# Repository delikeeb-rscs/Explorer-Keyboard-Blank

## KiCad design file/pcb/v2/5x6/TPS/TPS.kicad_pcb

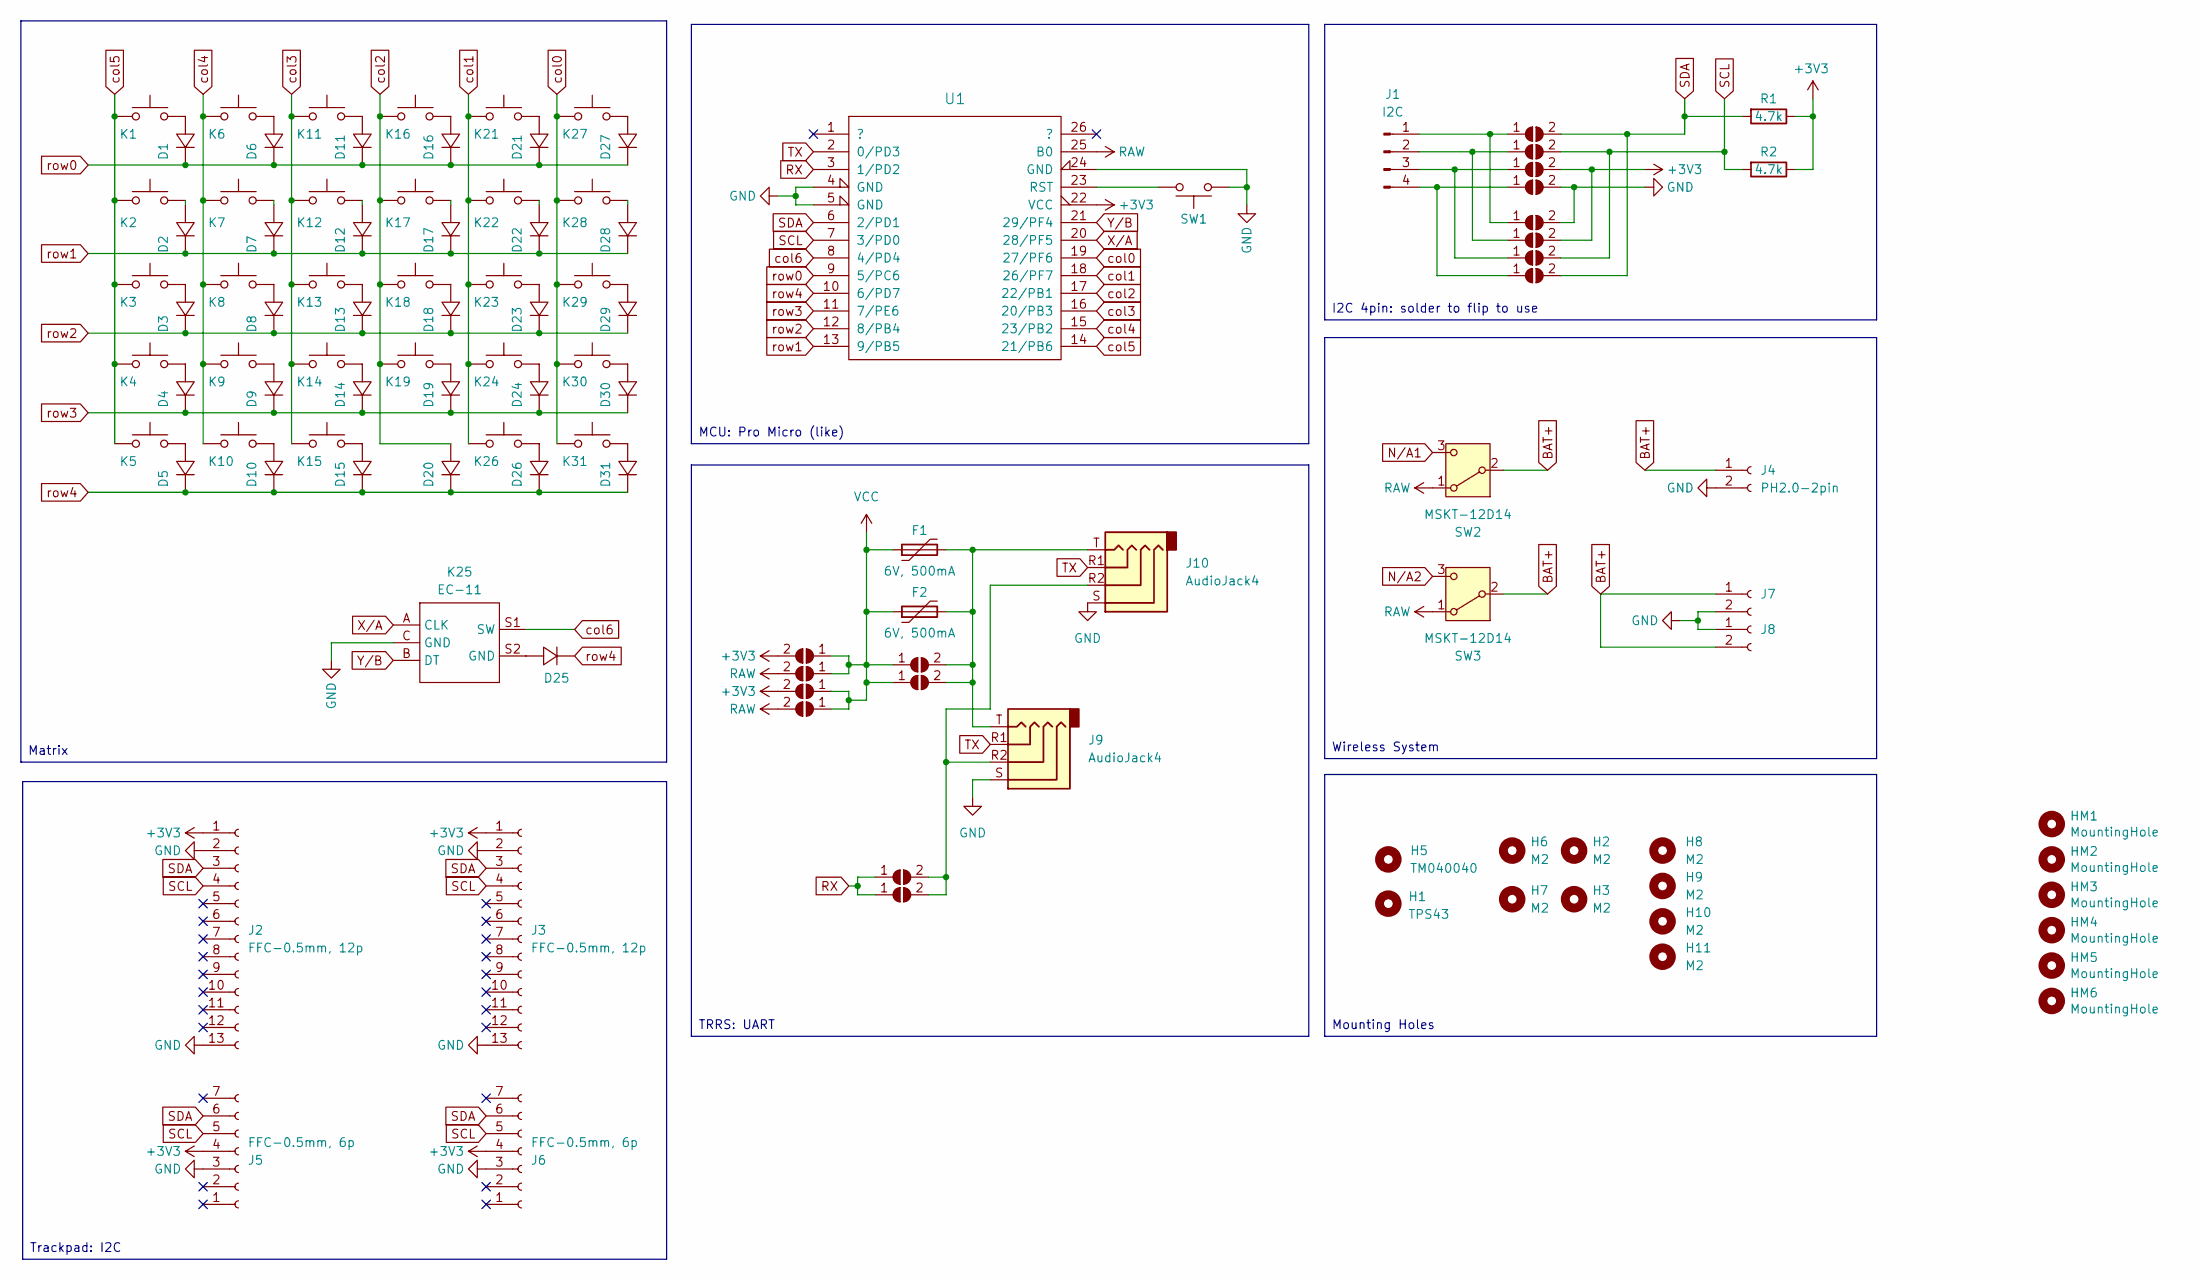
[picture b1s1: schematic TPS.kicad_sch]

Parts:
D1, D2, D3, D4, D5, D6, D7, D8, D9, D10, D11, D12, D13, D14, D15, D16, D17, D18, D19, D20, D21, D22, D23, D24, D25, D26, D27, D28, D29, D30, D31: 1N4148_SMD; D_SOD-123_handsolder_dual
F1, F2: 6V, 500mA; Fuse_0805_2012Metric
H1: TPS43; Azoteq_TPS43_201A_S
H2, H3, H6, H7, H8, H9, H10, H11: M2; MountingHole_2.2mm_M2
H5: TM040040; Trackpad_Cirque_TM040040
HM1, HM2, HM3, HM4, HM5, HM6: MountingHole; MountingHole_2.2mm_M2_ISO7380_Pad_noSilk
J1: I2C; PinHeader_1x04_P2.54mm_Vertical
J2, J3: FFC-0.5mm, 12p; Hirose_FH12-12S-0.5SH_1x12-1MP_P0.50mm_Horizontal
J4: PH2.0-2pin; JST_PH_S2B-PH-K_1x02_P2.00mm_Horizontal_dual
J5, J6: FFC-0.5mm, 6p; Hirose_FH12-6S-0.5SH_1x06-1MP_P0.50mm_Horizontal
J7, J8: PinHeader_1x02_P2.54mm_Vertical
J9: AudioJack4; TRRS-PJ-320A, dual side x2
J10: AudioJack4; TRRS-PJ-320A, dual side x2_3rd
JP1, JP2, JP3, JP4: PWR1; SolderJumper-2_P1.3mm_Open_Pad1.0x1.5mm
JP5, JP6, JP7, JP8, JP9, JP10, JP11, JP12: PWR1; SolderJumper-2_P1.3mm_Open_RoundedPad1.0x1.5mm
JP13, JP14: RX; SolderJumper-2_P1.3mm_Open_RoundedPad1.0x1.5mm
JP15, JP16: VCC; SolderJumper-2_P1.3mm_Open_Pad1.0x1.5mm
K1, K2, K3, K4, K6, K7, K8, K9, K11, K12, K13, K14, K15, K16, K17, K18, K19, K21, K22, K23, K24, K27, K28, K29, K30: SW_Push; SW_hotswap_HLP_Plated_1u-reversible
K5, K10, K26, K31: SW_Push; SW_hotswap_HLP_Plated_1.25u-reversible
K25: EC-11; RotaryEncoder_EC11
R1, R2: 4.7k; R_Axial_DIN0204_L3.6mm_D1.6mm_P7.62mm_Horizontal
SW1: SW_Push; ResetSW_1side
SW2, SW3: MSKT-12D14; SW_SPDT_MSKT-12D14_SMD_dual
U1: MCU_ProMicro_13p; MCU_ProMicro_13p_dual

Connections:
+3V3: J2.1, J3.1, J5.4, J6.4, JP1.2 (B), JP3.2 (B), JP7.2 (B), JP10.2 (B), R1.1, R2.1, U1.22 (VCC)
BAT+: J4.1, J7.1, J8.2, SW2.2 (B), SW3.2 (B)
GND: J2.2, J2.13, J3.2, J3.13, J4.2, J5.3, J6.3, J7.2, J8.1, J9.S, J10.S, JP8.2 (B), JP9.2 (B), K25.C (GND), SW1.1, U1.4 (GND), U1.5 (GND), U1.24 (GND)
unnamed: D1.2, K1.2
unnamed: D2.2, K2.2
unnamed: D3.2, K3.2
unnamed: D4.2, K4.2
unnamed: D5.2, K5.2
unnamed: D6.2, K6.2
unnamed: D7.2, K7.2
unnamed: D8.2, K8.2
unnamed: D9.2, K9.2
unnamed: D10.2, K10.2
unnamed: D11.2, K11.2
unnamed: D12.2, K12.2
unnamed: D13.2, K13.2
unnamed: D14.2, K14.2
unnamed: D15.2, K15.2
unnamed: D16.2, K16.2
unnamed: D17.2, K17.2
unnamed: D18.2, K18.2
unnamed: D19.2, K19.2
unnamed: D21.2, K21.2
unnamed: D22.2, K22.2
unnamed: D23.2, K23.2
unnamed: D24.2, K24.2
unnamed: D25.2, K25.S2 (GND)
unnamed: D26.2, K26.2
unnamed: D27.2, K27.2
unnamed: D28.2, K28.2
unnamed: D29.2, K29.2
unnamed: D30.2, K30.2
unnamed: D31.2, K31.2
unnamed: J1.1, JP5.1 (A), JP9.1 (A)
unnamed: J1.2, JP6.1 (A), JP10.1 (A)
unnamed: J1.3, JP7.1 (A), JP11.1 (A)
unnamed: J1.4, JP8.1 (A), JP12.1 (A)
unnamed: J9.R2, J10.R2, JP13.2 (B), JP14.2 (B)
unnamed: F1.2, F2.2, J9.T, J10.T, JP15.2 (B), JP16.2 (B)
unnamed: SW1.2, U1.23 (RST)
N/A1: SW2.3 (C)
N/A2: SW3.3 (C)
RAW: JP2.2 (B), JP4.2 (B), SW2.1 (A), SW3.1 (A), U1.25 (B0)
RX: JP13.1 (A), JP14.1 (A), U1.3 (1/PD2)
SCL: J2.4, J3.4, J5.5, J6.5, JP6.2 (B), JP11.2 (B), R2.2, U1.7 (3/PD0)
SDA: J2.3, J3.3, J5.6, J6.6, JP5.2 (B), JP12.2 (B), R1.2, U1.6 (2/PD1)
TX: J9.R1, J10.R1, U1.2 (0/PD3)
VCC: F1.1, F2.1, JP1.1 (A), JP2.1 (A), JP3.1 (A), JP4.1 (A), JP15.1 (A), JP16.1 (A)
X/A: K25.A (CLK), U1.20 (28/PF5)
Y/B: K25.B (DT), U1.21 (29/PF4)
col0: K27.1, K28.1, K29.1, K30.1, K31.1, U1.19 (27/PF6)
col1: K21.1, K22.1, K23.1, K24.1, K26.1, U1.18 (26/PF7)
col2: D20.2, K16.1, K17.1, K18.1, K19.1, U1.17 (22/PB1)
col3: K11.1, K12.1, K13.1, K14.1, K15.1, U1.16 (20/PB3)
col4: K6.1, K7.1, K8.1, K9.1, K10.1, U1.15 (23/PB2)
col5: K1.1, K2.1, K3.1, K4.1, K5.1, U1.14 (21/PB6)
col6: K25.S1 (SW), U1.8 (4/PD4)
row0: D1.1, D6.1, D11.1, D16.1, D21.1, D27.1, U1.9 (5/PC6)
row1: D2.1, D7.1, D12.1, D17.1, D22.1, D28.1, U1.13 (9/PB5)
row2: D3.1, D8.1, D13.1, D18.1, D23.1, D29.1, U1.12 (8/PB4)
row3: D4.1, D9.1, D14.1, D19.1, D24.1, D30.1, U1.11 (7/PE6)
row4: D5.1, D10.1, D15.1, D20.1, D25.1, D26.1, D31.1, U1.10 (6/PD7)

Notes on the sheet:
I2C 4pin: solder to flip to use
Trackpad: I2C
Mounting Holes
TRRS: UART
Wireless System
MCU: Pro Micro (like)
Matrix

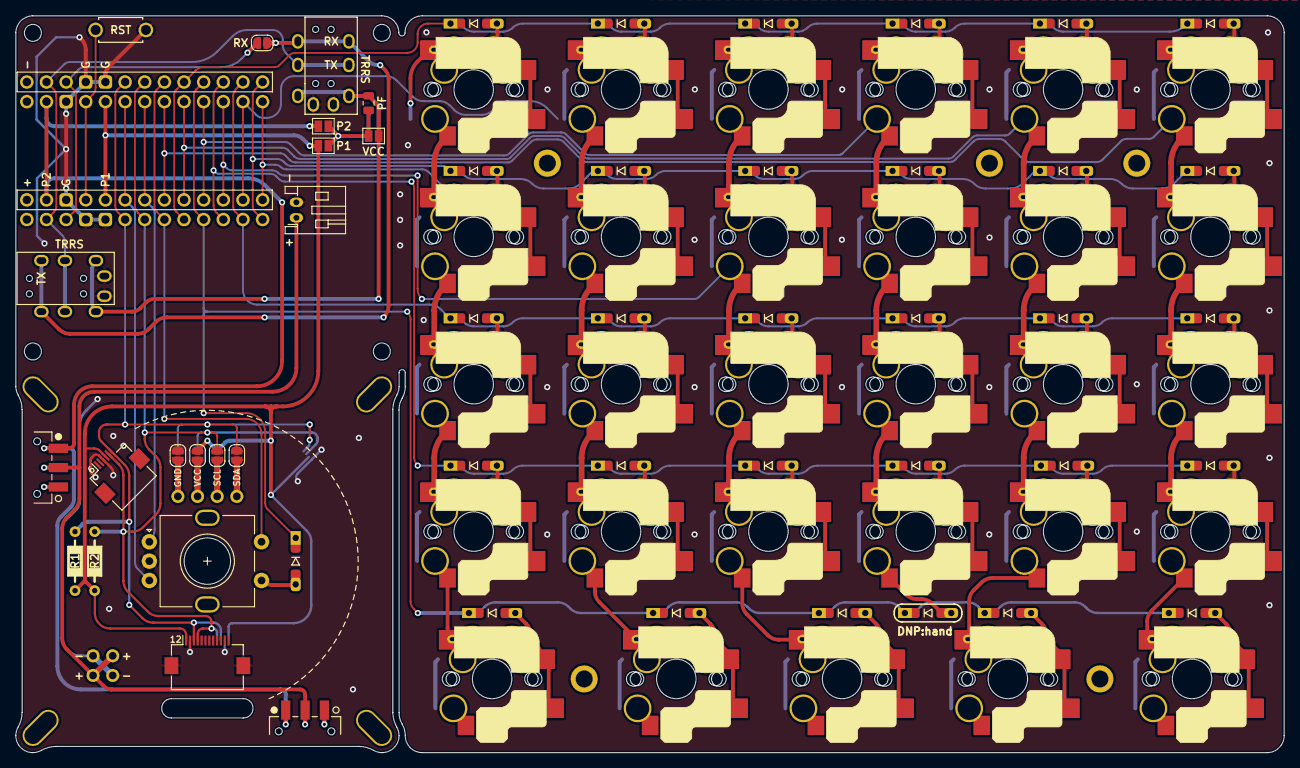
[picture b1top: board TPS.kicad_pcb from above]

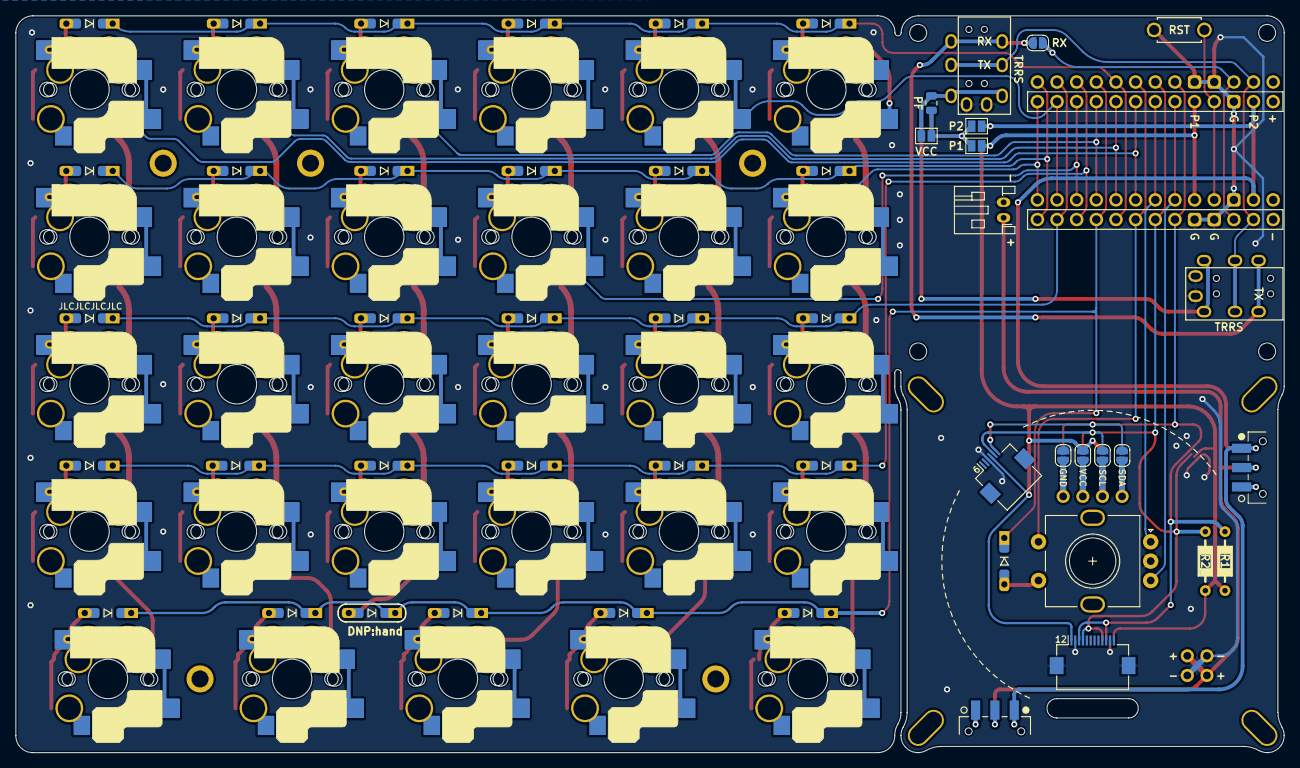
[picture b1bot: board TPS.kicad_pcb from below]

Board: 2 copper layers, 164.0 x 95.2 mm, 110 parts (12 on the bottom side), 60 nets.

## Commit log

2026-05-14 Remove invalid Windows log filename
2026-05-14 manufacturered with JLCPCB
